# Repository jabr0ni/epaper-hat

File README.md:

# E-Paper Business Card?

My idea is to create a type of business card with an e-paper display, where I can program some image/text content onto it. I also want to (in later revisions once the prototype is working) add a button on the back that can toggle to different images. Also have thought about adding one or two sensors (depending on space) such as a gyro and/or comms module. I plan on interfacing this with an STM32L4 MCU (have a Nucleo L433RC). Code for that has been started in this repo.

## PCB
This is my first PCB I've designed by myself from scratch, so any feedback is encouraged 😊
### Track layout

### Front + Back 3D

## BOM
| Reference        | Qty | Value            | Manufacturer Part No.         |
|------------------|-----|------------------|--------------------------------|
| C1, C2, C4, C5, C7, C9, C10 | 7   | 1u/50V           | MBASU168AB5105KTNA01           |
| C3, C13          | 2   | 0.1u/50V         | MAJCU168BB7104KTEA01           |
| C6, C8, C14      | 3   | 1u/25V           | MAJCT168BB7105KTEA01           |
| C11, C12         | 2   | CL21A475KBQNNNE  | CL21A475KBQNNNE                |
| D1, D2, D3       | 3   | MBR0530          | MBR0540T1G                     |
| J1               | 1   | Conn_01x08       | TSW-103-07-T-D                 |
| J2               | 1   | Conn_01x24       | MTSW-112-07-F-D-195            |
| J3               | 1   | SFV24R-1STBE1HLF | SFV24R-1STBE1HLF               |
| L1               | 1   | L_Iron           | LPS4018-104MRC                 |
| Q1               | 1   | Si1308EDL        | SI1308EDL-T1-BE3               |
| Q2               | 1   | AO3401A          | SSM3J340R,LF                   |
| Q3               | 1   | S8050            | SS8050DBU                      |
| R1               | 1   | 10k              | CRCW060310K0FKEI               |
| R2               | 1   | 3R               | CRCW06033R00FKEAC              |
| R3               | 1   | 1k               | CRCW06031K00FKED               |
| R6               | 1   | 1K               | CRCW06031K00FKED               |
| R7               | 1   | 10K              | CRCW060310K0FKEI               |
| R8, R9, R10      | 3   | 47K              | CRCW060347K0FKED               |
| R11              | 1   | 100K             | CRCW0603100KFKEE               |
| U1               | 1   | RT9193-33GB      | RT9193-33GB                    |
| U2               | 1   | TXB0108PW        | TXB0108PWR                     |
|----------------------------------------------------------------------------|

# Prototyped Boards
I recently had my custom PCB prototyped through [PCBWay](https://www.pcbway.com/), and I am very impressed with the overall quality and service. From the start, their customer support was excellent—clear, responsive, and proactive in keeping me updated on the progress of my order. It was reassuring to receive regular communication at each stage of the process, from file checks through to production and shipping.

The boards themselves came out great. The soldering work is clean, precise, and of consistently high quality. I inspected the joints and pads closely, and everything was well aligned with no visible defects or irregularities. The overall finish of the boards, from the silkscreen to the copper traces, is sharp and professional. It’s clear that PCBWay places strong emphasis on both manufacturing quality and attention to detail.

What stood out most to me was how smooth the experience was. Even as a prototype run, the boards feel production-ready, giving me confidence to move forward with testing and further development. For anyone looking for reliable PCB prototyping with excellent communication and workmanship, I would highly recommend PCBWay. I’ll definitely be returning for future projects.

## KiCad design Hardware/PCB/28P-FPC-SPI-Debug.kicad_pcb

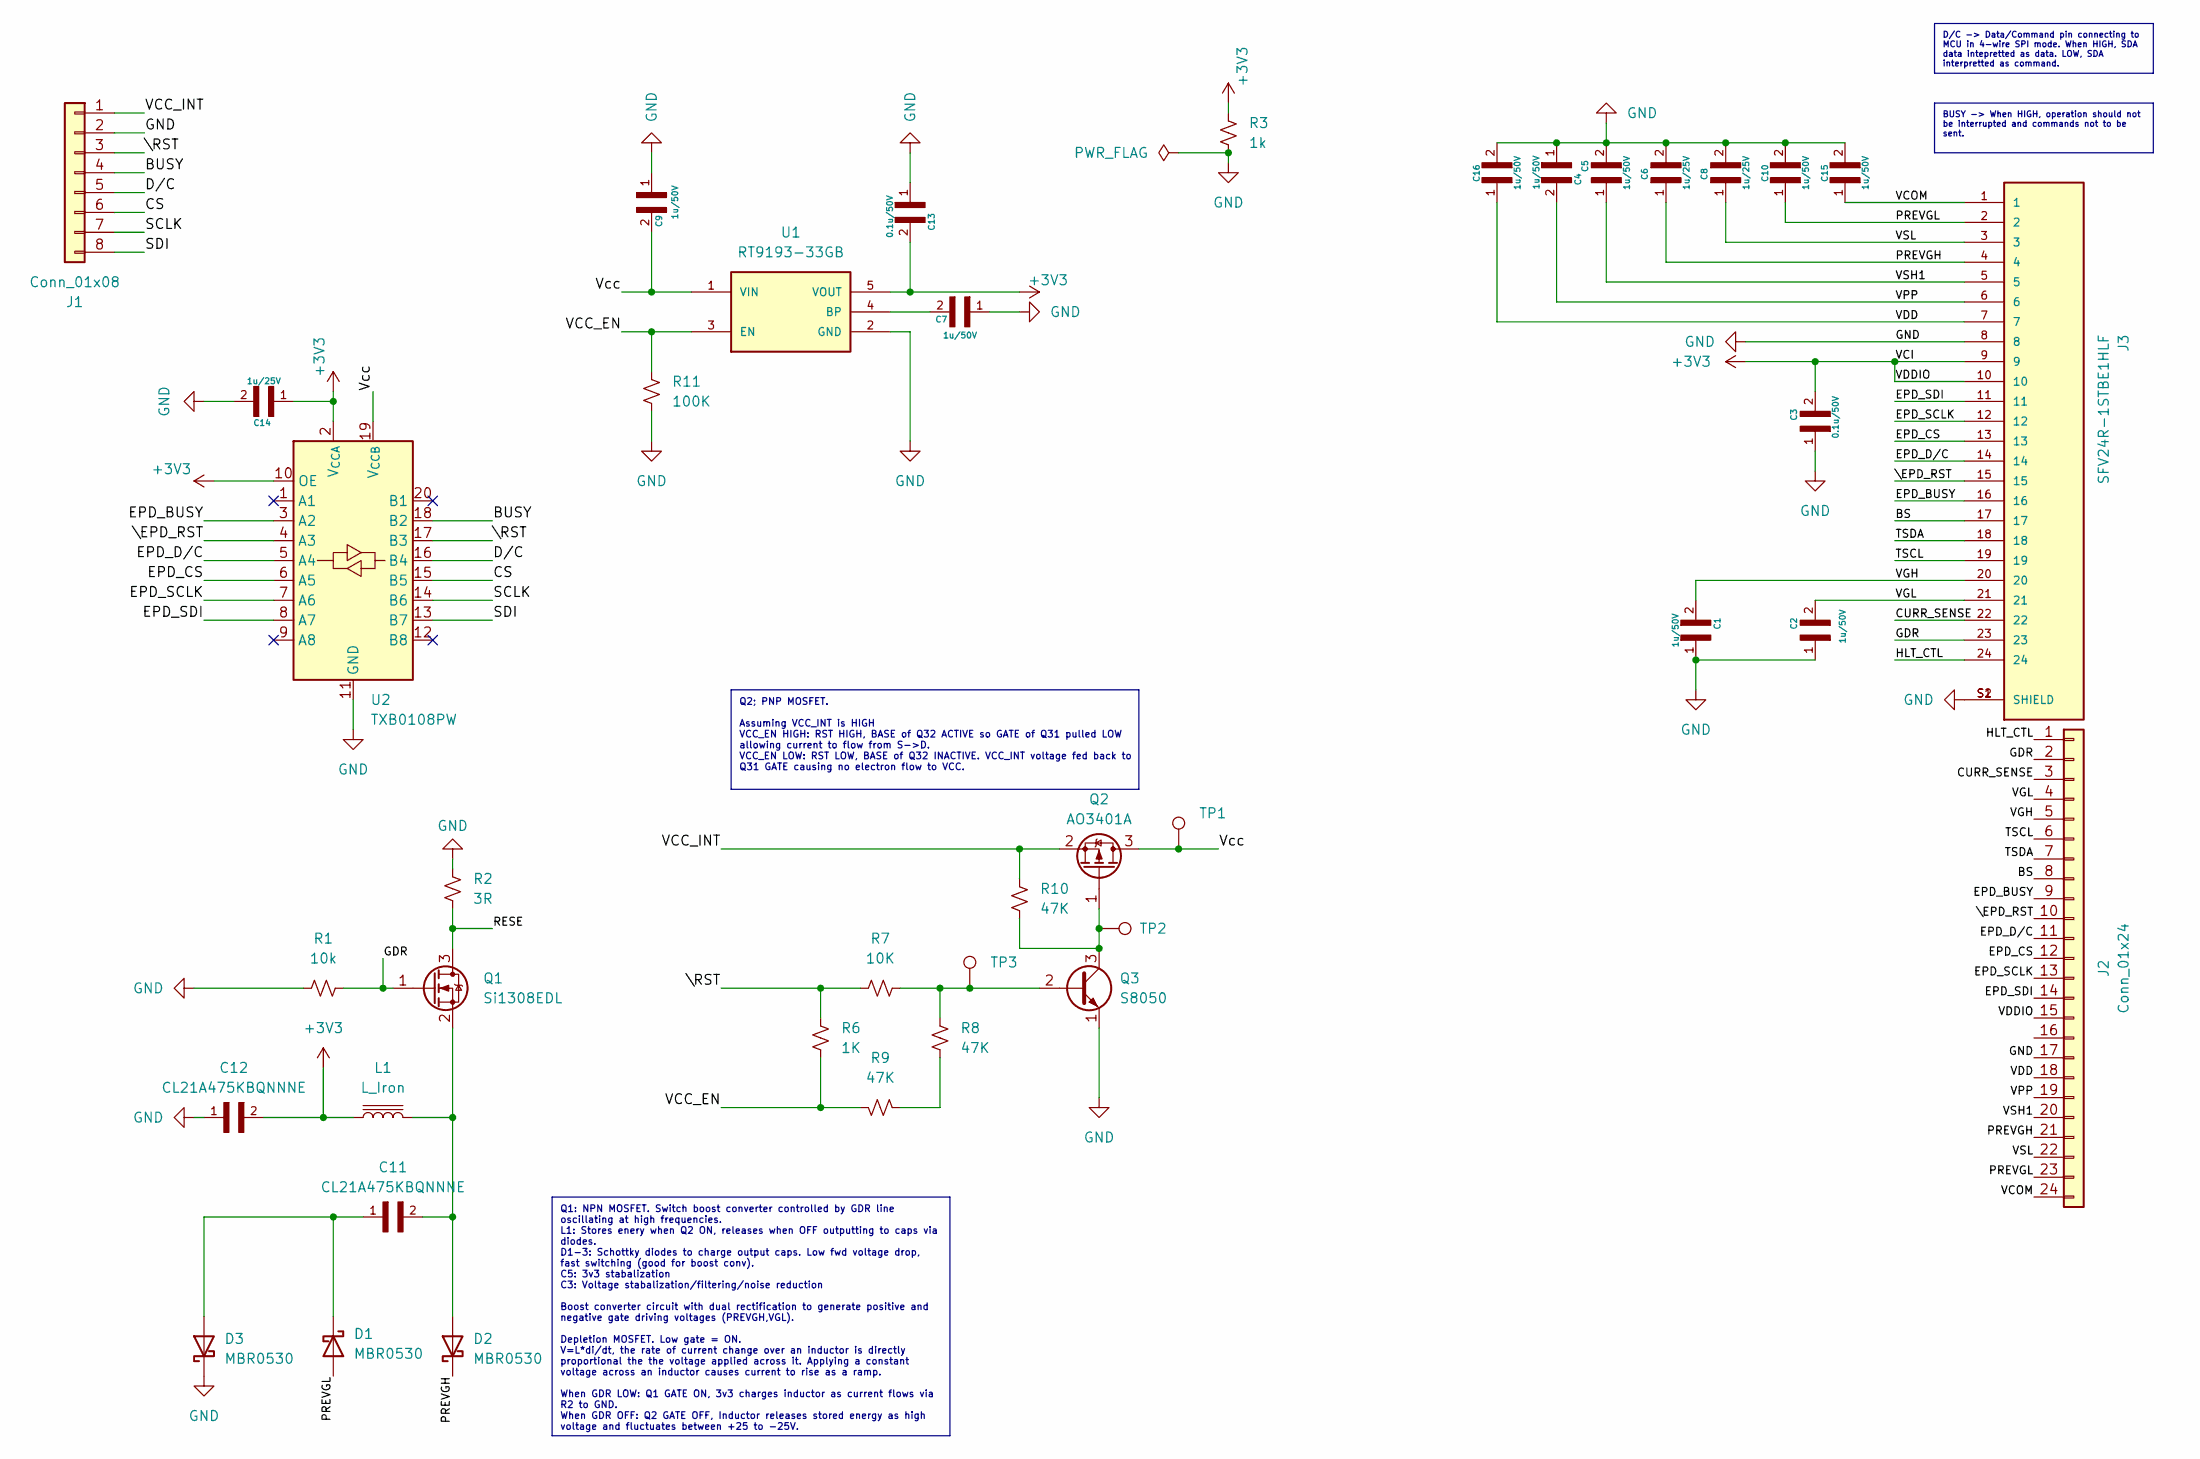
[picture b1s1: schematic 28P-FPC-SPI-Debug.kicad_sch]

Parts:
C1, C2, C4, C5, C7, C9, C10, C15, C16: 1u/50V; C_0603_1608Metric_Pad1.08x0.95mm_HandSolder; PARTREV NA
C3, C13: 0.1u/50V; C_0603_1608Metric_Pad1.08x0.95mm_HandSolder; PARTREV NA
C6, C8, C14: 1u/25V; CAPC1608X90N; PARTREV APR.09.2024
C11, C12: CL21A475KBQNNNE; C_0805_2012Metric_Pad1.18x1.45mm_HandSolder
D1, D2, D3: MBR0530; D_SOD-123
J1: Conn_01x08; PinHeader_1x08_P2.54mm_Vertical
J2: Conn_01x24; PinHeader_2x12_P2.54mm_Vertical
J3: SFV24R-1STBE1HLF; GCT_FFC2B28-24-G; PARTREV A
L1: L_Iron; IND_LPS4018-104MRC
Q1: Si1308EDL; SOT-323_SC-70
Q2: AO3401A; SOT-23
Q3: S8050
R1: 10k; R_0603_1608Metric_Pad0.98x0.95mm_HandSolder
R2: 3R; R_0603_1608Metric_Pad0.98x0.95mm_HandSolder
R3: 1k; R_0603_1608Metric_Pad0.98x0.95mm_HandSolder
R6: 1K; R_0603_1608Metric_Pad0.98x0.95mm_HandSolder
R7: 10K; R_0603_1608Metric_Pad0.98x0.95mm_HandSolder
R8, R9, R10: 47K; R_0603_1608Metric_Pad0.98x0.95mm_HandSolder
R11: 100K; R_0603_1608Metric_Pad0.98x0.95mm_HandSolder
TP1, TP2, TP3: TestPoint_THTPad_1.0x1.0mm_Drill0.5mm
U1: RT9193-33GB; SOT94P279X129-5N
U2: TXB0108PW; TSSOP-20_4.4x6.5mm_P0.65mm

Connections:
+3V3: C3.2, C12.2, C13.2, C14.1, J2.15, J3.9, J3.10, L1.1, R3.2, U1.5 (VOUT), U2.2 (V_{CCA}), U2.10 (OE)
/BS: J2.8, J3.17
/BUSY: J1.4, U2.18 (B2)
/CS: J1.6, U2.15 (B5)
/CURR_SENSE: J2.3, J3.22
/D/C: J1.5, U2.16 (B4)
/EPD_BUSY: J2.9, J3.16, U2.3 (A2)
/EPD_CS: J2.12, J3.13, U2.6 (A5)
/EPD_D/C: J2.11, J3.14, U2.5 (A4)
/EPD_SCLK: J2.13, J3.12, U2.7 (A6)
/EPD_SDI: J2.14, J3.11, U2.8 (A7)
/GDR: J2.2, J3.23, Q1.1 (G), R1.2
/HLT_CTL: J2.1, J3.24
/PREVGH: C6.1, D2.1 (K), J2.21, J3.4
/PREVGL: C10.1, D1.2 (A), J2.23, J3.2
/RESE: Q1.3 (D), R2.1
/SCLK: J1.7, U2.14 (B6)
/SDI: J1.8, U2.13 (B7)
/TSCL: J2.6, J3.19
/TSDA: J2.7, J3.18
/VCC_EN: R6.2, R9.1, R11.1, U1.3 (EN)
/VCC_INT: J1.1, Q2.2 (S), R10.2
/VCOM: C15.1, J2.24, J3.1
/VDD: C16.1, J2.18, J3.7
/VGH: C1.2, J2.5, J3.20
/VGL: C2.2, J2.4, J3.21
/VPP: C4.2, J2.19, J3.6
/VSH1: C5.1, J2.20, J3.5
/VSL: C8.1, J2.22, J3.3
/Vcc: C9.2, Q2.3 (D), TP1.1, U1.1 (VIN), U2.19 (V_{CCB})
/\EPD_RST: J2.10, J3.15, U2.4 (A3)
/\RST: J1.3, R6.1, R7.2, U2.17 (B3)
GND: C1.1, C2.1, C3.1, C4.1, C5.2, C6.2, C7.1, C8.2, C9.1, C10.2, C12.1, C13.1, C14.2, C15.2, C16.2, D3.1 (K), J1.2, J2.17, J3.8, J3.S1 (SHIELD), J3.S2 (SHIELD), Q3.1 (E), R1.1, R2.2, R3.1, R11.2, U1.2 (GND), U2.11 (GND)
unnamed: C11.1, D1.1 (K), D3.2 (A)
unnamed: C11.2, D2.2 (A), L1.2, Q1.2 (S)
unnamed: Q2.1 (G), Q3.3 (C), R10.1, TP2.1
unnamed: Q3.2 (B), R7.1, R8.2, TP3.1
unnamed: R8.1, R9.2
unnamed: C7.2, U1.4 (BP)

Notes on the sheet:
D/C -> Data/Command pin connecting to MCU in 4-wire SPI mode. When HIGH, SDA data intepretted as data. LOW, SDA interpretted as command.
Q1: NPN MOSFET. Switch boost converter controlled by GDR line oscillating at high frequencies. L1: Stores enery when Q2 ON, releases when OFF outputting to caps via diodes. D1-3: Schottky diodes to charge output caps. Low fwd voltage drop, fast switching (good for boost conv). C5: 3v3 stabalization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
BUSY -> When HIGH, operation should not be interrupted and commands not to be sent.
Q2; PNP MOSFET. Assuming VCC_INT is HIGH VCC_EN HIGH: RST HIGH, BASE of Q32 ACTIVE so GATE of Q31 pulled LOW allowing current to flow from S->D. VCC_EN LOW: RST LOW, BASE of Q32 INACTIVE. VCC_INT voltage fed back to Q31 GATE causing no electron flow to VCC.

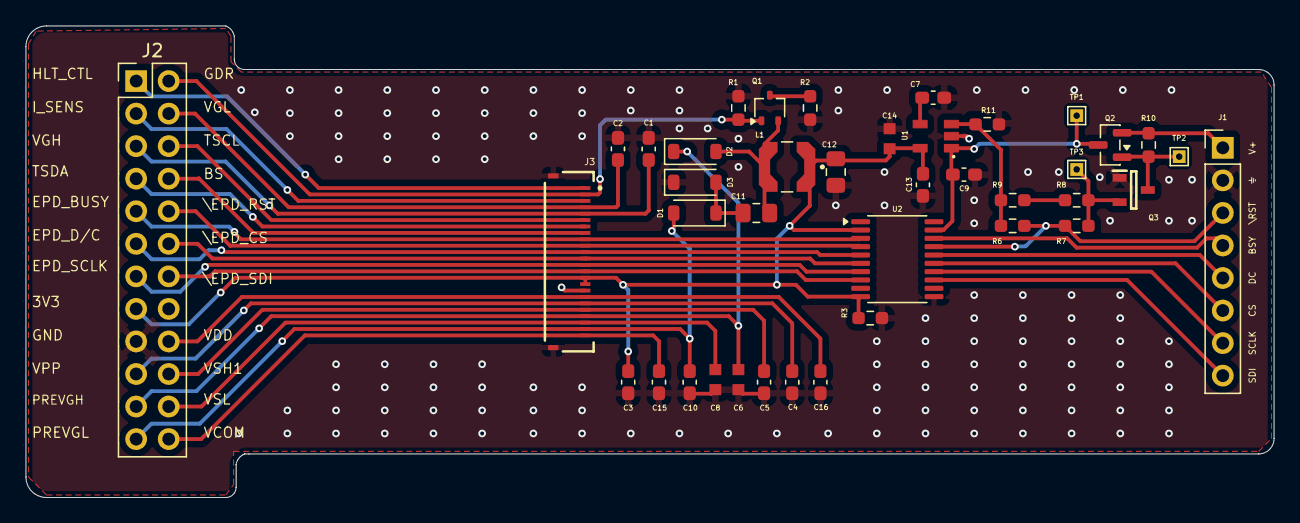
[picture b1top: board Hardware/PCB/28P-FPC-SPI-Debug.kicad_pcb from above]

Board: 2 copper layers, 97.4 x 36.8 mm, 40 parts (0 on the bottom side), 39 nets.

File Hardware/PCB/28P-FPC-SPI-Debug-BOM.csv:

Reference,Qty,Value,DNP,Exclude from BOM,Exclude from Board,Footprint,Datasheet,Mouser No:,Mfr. No:
"C1,C2,C4,C5,C7,C9,C10",7,1u/50V,,,,capacitors-cam:CAPC2012X140N,,963-BASU168AB5105KT,MBASU168AB5105KTNA01
"C3,C13",2,0.1u/50V,,,,capacitors-cam:CAPC2012X140N,,963-MAJCU168BB7104KT,MAJCU168BB7104KTEA01
"C6,C8,C14",3,1u/25V,,,,capacitors-cam:CAPC1608X90N,,963-MAJCT168BB7105KT,MAJCT168BB7105KTEA01
"C11,C12",2,CL21A475KBQNNNE,,,,capacitors-cam:CAPC2012X140N,,187-CL21A475KBQNNNE,CL21A475KBQNNNE
"D1,D2,D3",3,MBR0530,,,,Diode_SMD:D_SOD-123,http://www.mccsemi.com/up_pdf/MBR0520~MBR0580(SOD123).pdf,863-MBR0540T1G,MBR0540T1G
J1,1,Conn_01x08,,,,Connector_Samtec_HLE_THT:Samtec_HLE-104-02-xx-DV-TE_2x04_P2.54mm_Horizontal,~,200-TSW10307TD,TSW-103-07-T-D
J2,1,Conn_01x24,,,,Connector_PinHeader_2.54mm:PinHeader_2x12_P2.54mm_Vertical,~,200-MTSW-11207FD195,MTSW-112-07-F-D-195
J3,1,SFV24R-1STBE1HLF,,,,Connectors-cam:AMPHENOL_SFV24R-1STBE1HLF,,649-SFV24R-1STBE1HLF,SFV24R-1STBE1HLF
L1,1,L_Iron,,,,inductors:IND_LPS4018-104MRC,~,994-LPS4018-104MRC,LPS4018-104MRC
Q1,1,Si1308EDL,,,,Package_TO_SOT_SMD:SOT-323_SC-70,https://www.vishay.com/docs/63399/si1308edl.pdf,78-SI1308EDL-T1-BE3,SI1308EDL-T1-BE3
Q2,1,AO3401A,,,,Package_TO_SOT_SMD:SOT-23,http://www.aosmd.com/pdfs/datasheet/AO3401A.pdf,757-SSM3J340RLF,"SSM3J340R,LF"
Q3,1,S8050,,,,Package_TO_SOT_THT:TO-92_Inline,http://www.unisonic.com.tw/datasheet/S8050.pdf,512-SS8050DBU,SS8050DBU
R1,1,10k,,,,Resistor_SMD:R_0603_1608Metric_Pad0.98x0.95mm_HandSolder,~,71-CRCW060347K0FKED,CRCW060310K0FKEI
R2,1,3R,,,,Resistor_SMD:R_0603_1608Metric_Pad0.98x0.95mm_HandSolder,~,71-CRCW060310K0FKEI,CRCW06033R00FKEAC
R3,1,1k,,,,Resistor_SMD:R_0603_1608Metric_Pad0.98x0.95mm_HandSolder,~,71-CRCW0603100KFKEE,CRCW06031K00FKED
R6,1,1K,,,,Resistor_SMD:R_0603_1608Metric_Pad0.98x0.95mm_HandSolder,~,71-CRCW06031K00FKED,CRCW06031K00FKED
R7,1,10K,,,,Resistor_SMD:R_0603_1608Metric_Pad0.98x0.95mm_HandSolder,~,71-CRCW06033R00FKEAC,CRCW060310K0FKEI
"R8,R9,R10",3,47K,,,,Resistor_SMD:R_0603_1608Metric_Pad0.98x0.95mm_HandSolder,~,71-CRCW060347K0FKED,CRCW060347K0FKED
R11,1,100K,,,,Resistor_SMD:R_0603_1608Metric_Pad0.98x0.95mm_HandSolder,~,71-CRCW0603100KFKEE,CRCW0603100KFKEE
U1,1,RT9193-33GB,,,,VoltageRegulators:SOT94P279X129-5N,,835-RT9193-33GB,RT9193-33GB
U2,1,TXB0108PW,,,,Package_SO:TSSOP-20_4.4x6.5mm_P0.65mm,http://www.ti.com/lit/ds/symlink/txb0108.pdf,595-TXB0108PWR,TXB0108PWR

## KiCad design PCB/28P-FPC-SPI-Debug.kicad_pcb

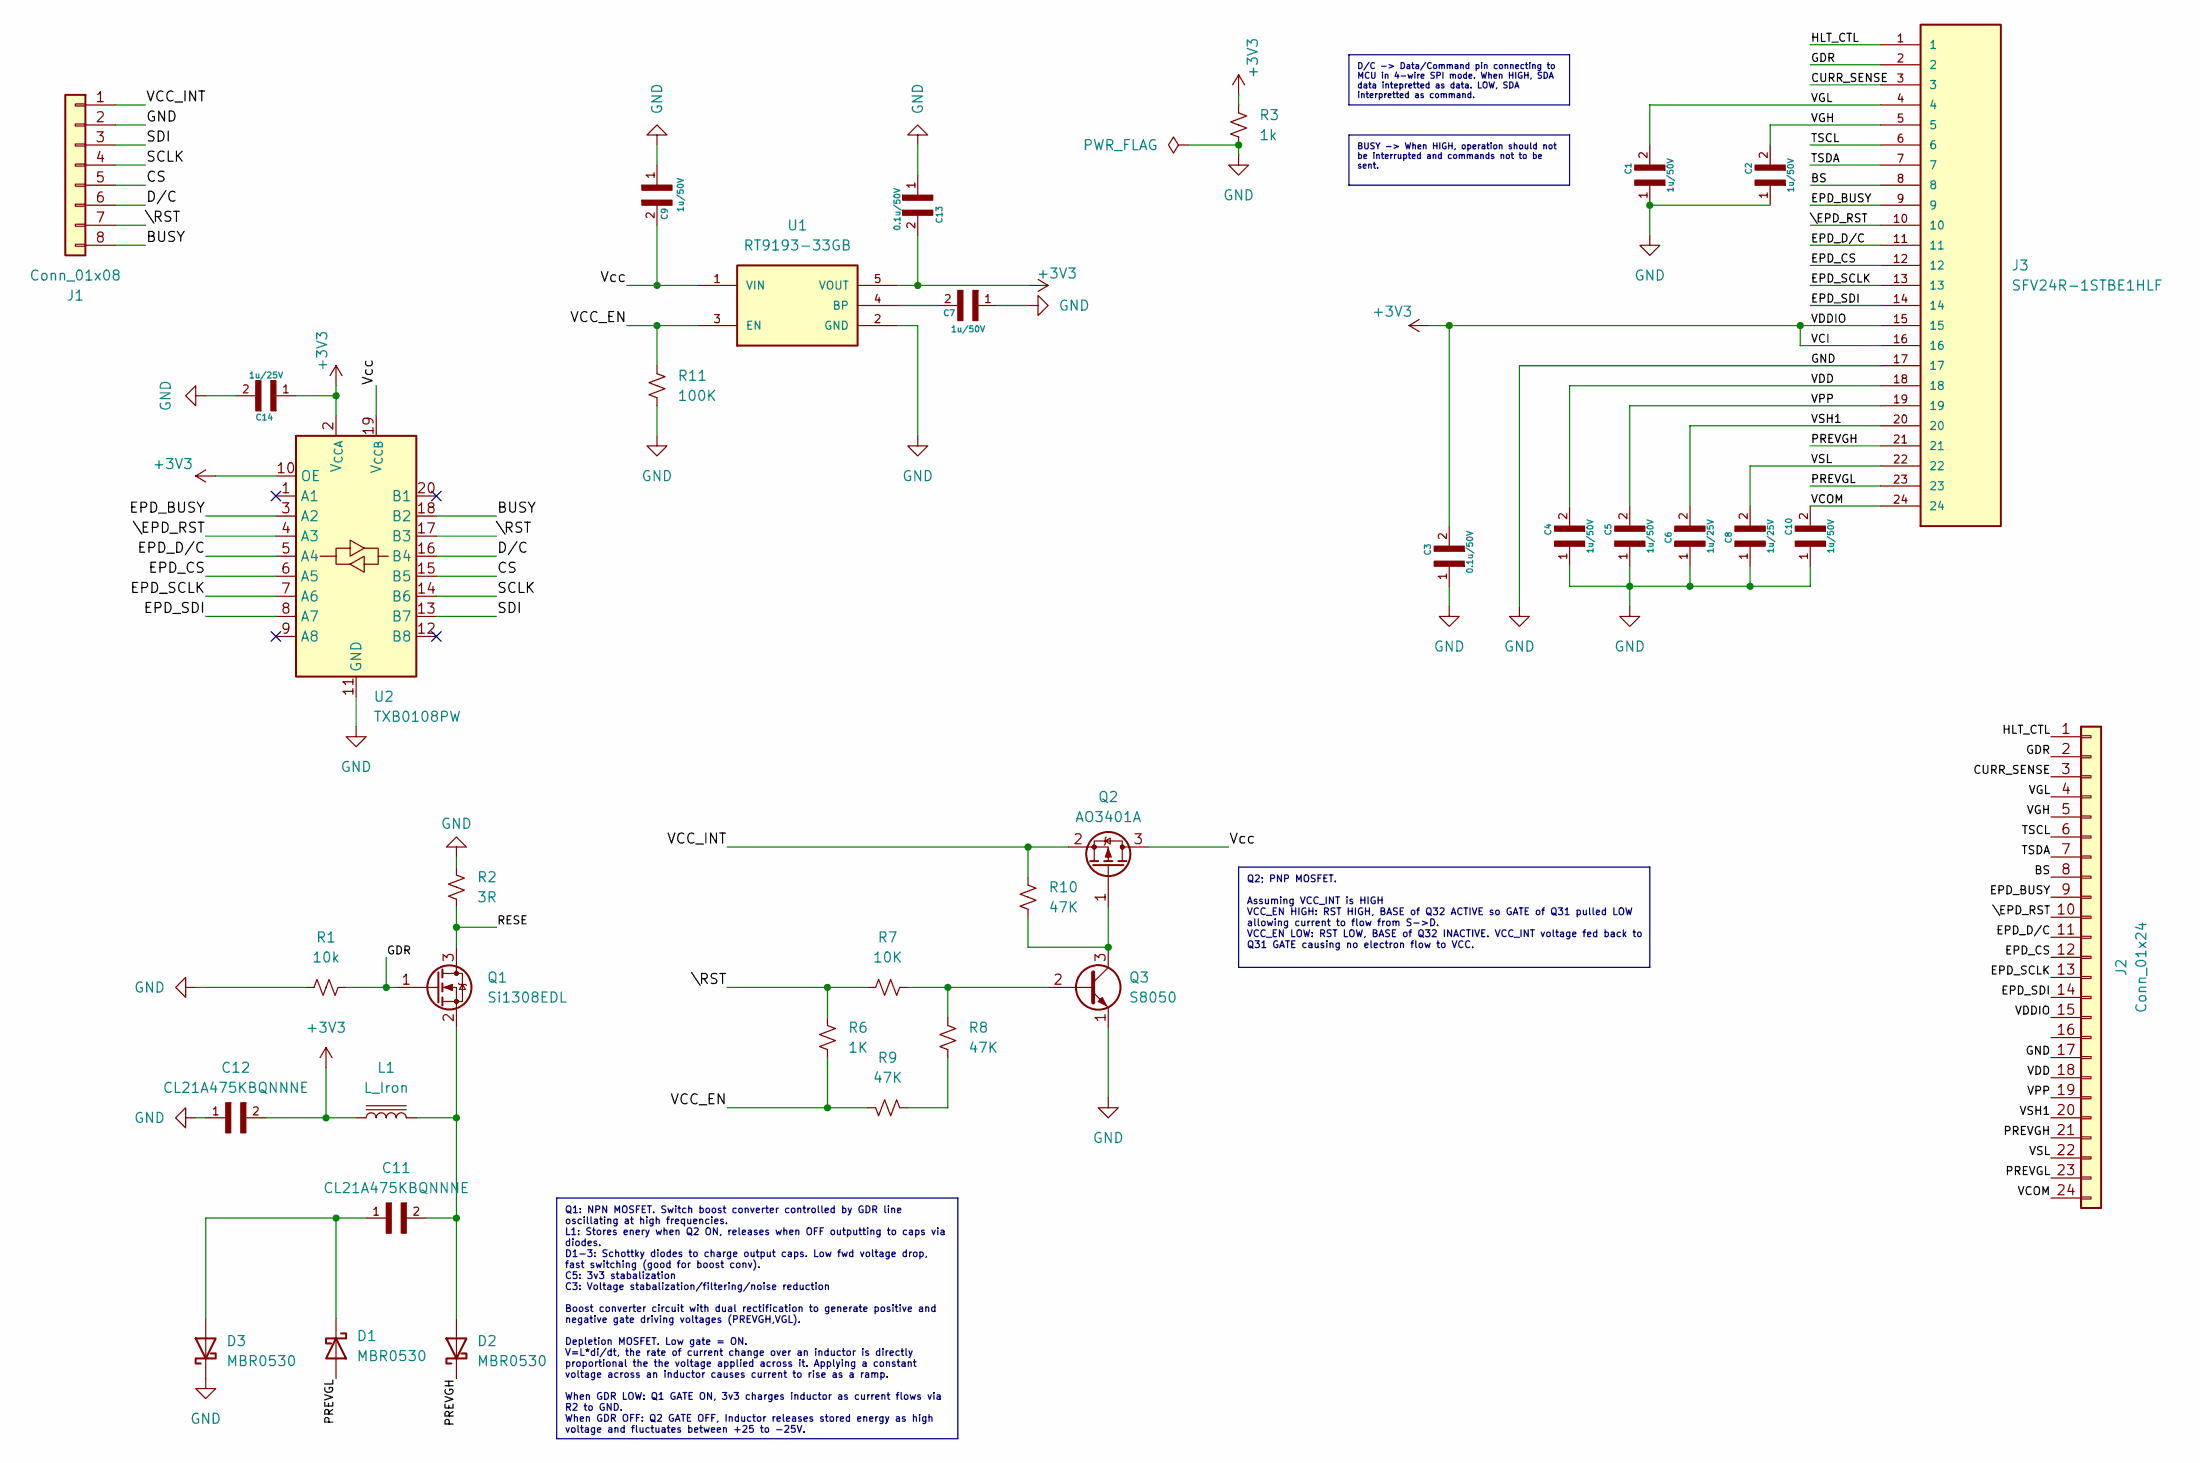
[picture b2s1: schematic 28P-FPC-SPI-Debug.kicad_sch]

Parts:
C1, C2, C4, C5, C7, C9, C10: 1u/50V; CAPC2012X140N; PARTREV NA
C3, C13: 0.1u/50V; CAPC2012X140N; PARTREV NA
C6, C8, C14: 1u/25V; CAPC1608X90N; PARTREV APR.09.2024
C11, C12: CL21A475KBQNNNE; CAPC2012X140N
D1, D2, D3: MBR0530; D_SOD-123
J1: Conn_01x08; Samtec_HLE-104-02-xx-DV-TE_2x04_P2.54mm_Horizontal
J2: Conn_01x24; PinHeader_2x12_P2.54mm_Vertical
J3: SFV24R-1STBE1HLF; AMPHENOL_SFV24R-1STBE1HLF; PARTREV B
L1: L_Iron; IND_LPS4018-104MRC
Q1: Si1308EDL; SOT-323_SC-70
Q2: AO3401A; SOT-23
Q3: S8050; TO-92_Inline
R1: 10k; R_0603_1608Metric_Pad0.98x0.95mm_HandSolder
R2: 3R; R_0603_1608Metric_Pad0.98x0.95mm_HandSolder
R3: 1k; R_0603_1608Metric_Pad0.98x0.95mm_HandSolder
R6: 1K; R_0603_1608Metric_Pad0.98x0.95mm_HandSolder
R7: 10K; R_0603_1608Metric_Pad0.98x0.95mm_HandSolder
R8, R9, R10: 47K; R_0603_1608Metric_Pad0.98x0.95mm_HandSolder
R11: 100K; R_0603_1608Metric_Pad0.98x0.95mm_HandSolder
U1: RT9193-33GB; SOT94P279X129-5N
U2: TXB0108PW; TSSOP-20_4.4x6.5mm_P0.65mm

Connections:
+3V3: C3.2, C12.2, C13.2, C14.1, J2.15, J3.15, J3.16, L1.1, R3.2, U1.5 (VOUT), U2.2 (V_{CCA}), U2.10 (OE)
/BS: J2.8, J3.8
/BUSY: J1.8, U2.18 (B2)
/CS: J1.5, U2.15 (B5)
/CURR_SENSE: J2.3, J3.3
/D/C: J1.6, U2.16 (B4)
/EPD_BUSY: J2.9, J3.9, U2.3 (A2)
/EPD_CS: J2.12, J3.12, U2.6 (A5)
/EPD_D/C: J2.11, J3.11, U2.5 (A4)
/EPD_SCLK: J2.13, J3.13, U2.7 (A6)
/EPD_SDI: J2.14, J3.14, U2.8 (A7)
/GDR: J2.2, J3.2, Q1.1 (G), R1.2
/HLT_CTL: J2.1, J3.1
/PREVGH: D2.1 (K), J2.21, J3.21
/PREVGL: D1.2 (A), J2.23, J3.23
/RESE: Q1.3 (D), R2.1
/SCLK: J1.4, U2.14 (B6)
/SDI: J1.3, U2.13 (B7)
/TSCL: J2.6, J3.6
/TSDA: J2.7, J3.7
/VCC_EN: R6.2, R9.1, R11.1, U1.3 (EN)
/VCC_INT: J1.1, Q2.2 (S), R10.2
/VCOM: C10.2, J2.24, J3.24
/VDD: C4.2, J2.18, J3.18
/VGH: C2.2, J2.5, J3.5
/VGL: C1.2, J2.4, J3.4
/VPP: C5.2, J2.19, J3.19
/VSH1: C6.2, J2.20, J3.20
/VSL: C8.2, J2.22, J3.22
/Vcc: C9.2, Q2.3 (D), U1.1 (VIN), U2.19 (V_{CCB})
/\EPD_RST: J2.10, J3.10, U2.4 (A3)
/\RST: J1.7, R6.1, R7.2, U2.17 (B3)
GND: C1.1, C2.1, C3.1, C4.1, C5.1, C6.1, C7.1, C8.1, C9.1, C10.1, C12.1, C13.1, C14.2, D3.1 (K), J1.2, J2.17, J3.17, Q3.1 (E), R1.1, R2.2, R3.1, R11.2, U1.2 (GND), U2.11 (GND)
unnamed: C11.1, D1.1 (K), D3.2 (A)
unnamed: C11.2, D2.2 (A), L1.2, Q1.2 (S)
unnamed: Q2.1 (G), Q3.3 (C), R10.1
unnamed: Q3.2 (B), R7.1, R8.2
unnamed: R8.1, R9.2
unnamed: C7.2, U1.4 (BP)

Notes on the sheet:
D/C -> Data/Command pin connecting to MCU in 4-wire SPI mode. When HIGH, SDA data intepretted as data. LOW, SDA interpretted as command.
Q1: NPN MOSFET. Switch boost converter controlled by GDR line oscillating at high frequencies. L1: Stores enery when Q2 ON, releases when OFF outputting to caps via diodes. D1-3: Schottky diodes to charge output caps. Low fwd voltage drop, fast switching (good for boost conv). C5: 3v3 stabalization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
BUSY -> When HIGH, operation should not be interrupted and commands not to be sent.
Q2; PNP MOSFET. Assuming VCC_INT is HIGH VCC_EN HIGH: RST HIGH, BASE of Q32 ACTIVE so GATE of Q31 pulled LOW allowing current to flow from S->D. VCC_EN LOW: RST LOW, BASE of Q32 INACTIVE. VCC_INT voltage fed back to Q31 GATE causing no electron flow to VCC.

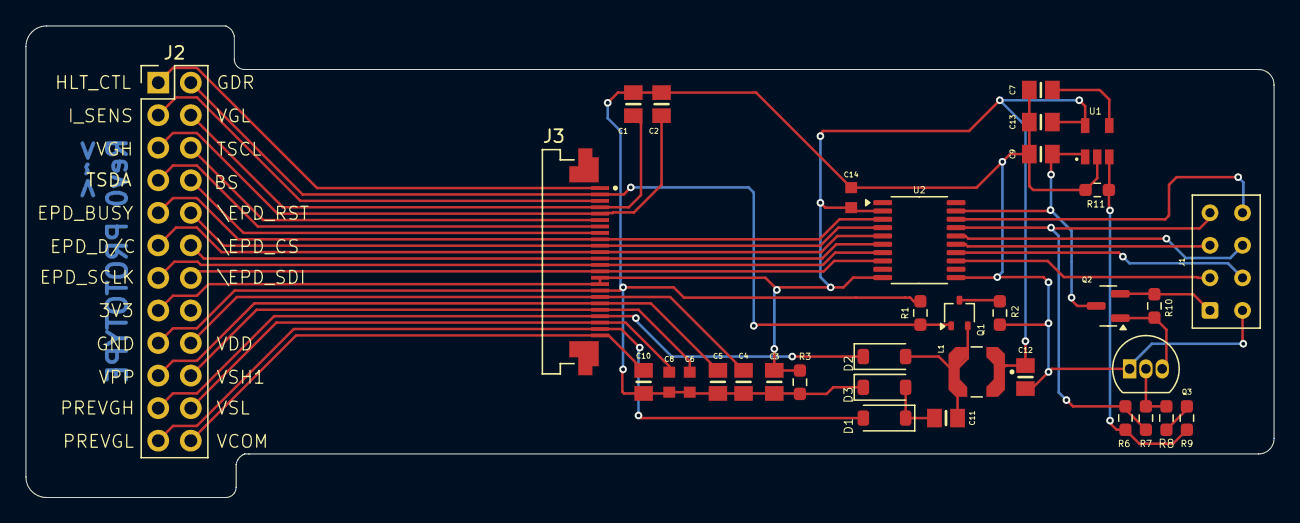
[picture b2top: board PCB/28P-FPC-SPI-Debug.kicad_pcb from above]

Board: 2 copper layers, 97.4 x 36.8 mm, 35 parts (0 on the bottom side), 39 nets.

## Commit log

2025-05-24 First commit. Just putting this up here.
2025-05-24 Added resources. Modified folder structure.
2025-05-29 Modified power switch circuit and added note. Added note for boost converter.
2025-05-30 Modified power enable circuit to v2.2 ref design and added note.
2025-05-31 Added voltage level shifter TXB018PW
2025-06-08 Added nets for TXB018PW. Resized PCB to size of 2.13in e-paper display with ~5mm excess on edges. Questionable part placement start.
2025-06-08 track placement, parts moved, nightmare fuel.
2025-06-08 track placement
2025-06-12 Added breakout 28pin header for debugging. Track cleanup. Changed 0603 footprint due to clearance violations. Increased board size to fit header.
2025-06-13 Moved some parts. Cleared ERC errors and warnings. Ready?
2025-06-19 Mouser BOM
2025-06-19 Added STM32 NUCLEO-L433RC project with basic pin assignments to J1 jumper on PCB for project start. Modified folder structure.
2025-06-26 Added waveshare submodule
2025-07-03 First commit for QT6 image converter app. Basic UI with load image push button, and image display in window panel.
2025-07-12 Imported OpenCV defines and libs.
2025-07-12 modified ImageHandler class with getters and setters. Converts Mat::cv to QImage. Added ImageProcessing class to handle opencv impage processing functions.
2025-07-12 Modified MainWindow class connect func to call class function instead of lambda.
2025-10-17 Modified J1 footprint to 1.7mm through hole. Added copper pours and GND via stitching for thermal relief. Plus some other stuff I can't remember. E-paper waveshare libs added to STM32 project. Projec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
2025-10-17 Missed files added from prev commit.
2025-10-17 removed waveshare repo. renamed stm32 project folder.
2025-10-17 Revise project description and PCB feedback request
    Updated the README to clarify the project idea and PCB design experience.
2025-11-08 Mirror pins on FPC connector. Reposition components. Copper pours
2025-11-08 Modified J3 FPC connector to top bottom connector FFC2B28-24-G.
2026-01-26 Modified FPC capacitor footprints to 0603 and 0805 due to production issues.
2026-01-26 Modified J2 to THT due to parts issue.
2026-02-01 Font size changes on some silkscreen prints. Footprint assignment mods for consistency.
